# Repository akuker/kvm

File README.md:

# kvm
Keyboard Video Monitor switch for vintage computers

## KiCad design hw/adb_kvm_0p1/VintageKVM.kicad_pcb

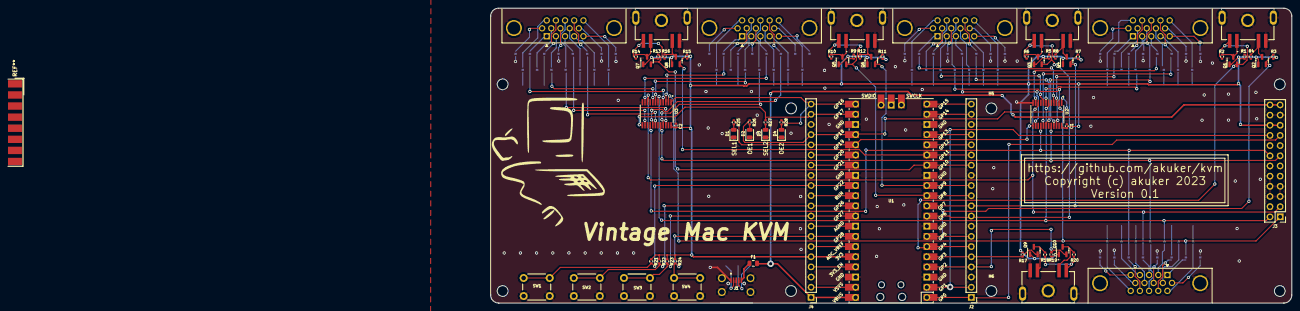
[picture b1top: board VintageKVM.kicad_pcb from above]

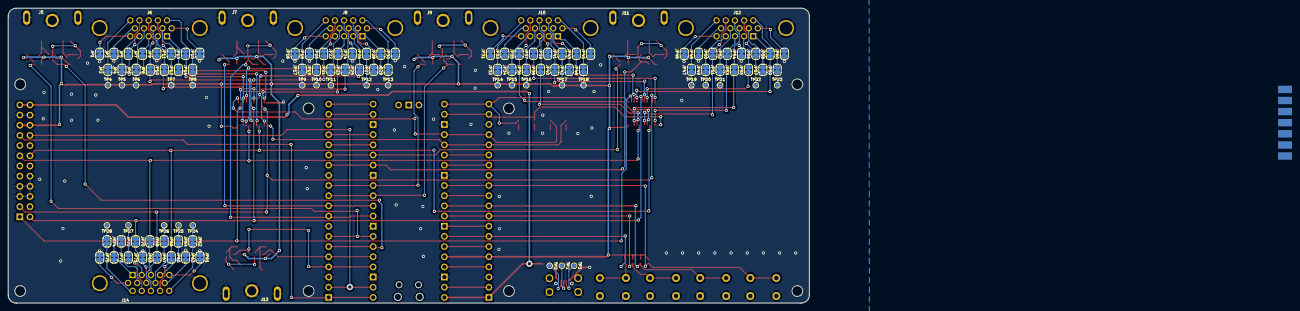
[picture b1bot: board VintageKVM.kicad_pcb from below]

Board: 2 copper layers, 200.0 x 73.6 mm, 177 parts (103 on the bottom side), 182 nets.

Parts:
C1, C2: 100nF; C_0402_1005Metric
D1, D2, D3, D4: LED_Small; LED_0805_2012Metric
F1: Polyfuse; Fuse_0805_2012Metric
H1, H2, H3, H4, H5, H6, H7, H8: MountingHole; MountingHole_2.7mm_M2.5
J1: Micro USB; U254051N4BH806
J2, J4: Conn_01x20_Pin; PinHeader_1x20_P2.54mm_Vertical
J3: Conn_02x10_Odd_Even; PinHeader_2x12_P2.54mm_Vertical
J5, J7, J9, J11, J13: CUI_MD2-40ST-SMT
J6, J8, J10, J12, J14: DE15_Receptacle_HighDensity_MountingHoles; DSUB-15-HD_Female_Horizontal_P2.29x1.98mm_EdgePinOffset3.03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
JP1, JP2, JP3, JP4, JP5, JP6, JP7, JP8, JP9, JP10, JP11, JP12, JP13, JP14, JP15, JP16, JP17, JP18, JP19, JP20, JP21, JP22, JP23, JP24, JP25, JP26, JP27, JP28, JP29, JP30, JP31, JP32, JP33, JP34, JP35, JP36, JP37, JP38, JP39, JP40, JP41, JP42, JP43, JP44, JP45, JP46, JP47, JP48, JP49, JP50, JP51, JP52, JP53, JP54, JP55, JP56, JP57, JP58, JP59, JP60, JP61, JP62, JP63, JP64, JP65, JP66, JP67, JP68, JP69, JP70, JP71, JP72, JP73, JP74, JP75: SolderJumper_2_Bridged; SolderJumper-2_P1.3mm_Bridged_RoundedPad1.0x1.5mm
Q1, Q2, Q3, Q4, Q5, Q6, Q7, Q8, Q9, Q10: BSS138; SOT-23
R1, R2, R3, R4, R5, R6, R7, R8, R9, R10, R11, R12, R13, R14, R15, R16, R17, R18, R19, R20, R21, R22, R23, R24, R25, R26, R27, R28: 10k; R_0402_1005Metric
SW1, SW2, SW3, SW4: SW_Push; SW_PUSH_6mm
TP1, TP2, TP3: TestPoint_Pad_D1.0mm
TP4, TP5, TP6, TP7, TP8, TP9, TP10, TP11, TP12, TP13, TP14, TP15, TP16, TP17, TP18, TP19, TP20, TP21, TP22, TP23, TP24, TP25, TP26, TP27, TP28: TestPoint_Small; TestPoint_Pad_D1.0mm
U1: Pico; RPi_Pico_SMD_TH
U2, U3: TS5V522CPWR; SOP65P640X120-24N

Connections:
3v3_EN: J4.4, U1.37 (3V3_EN)
+3V3: C1.1, C2.1, J3.19, J3.20, J4.5, Q1.1 (G), Q2.1 (G), Q3.1 (G), Q4.1 (G), Q5.1 (G), Q6.1 (G), Q7.1 (G), Q8.1 (G), Q9.1 (G), Q10.1 (G), R1.1, R3.1, R5.1, R7.1, R9.1, R11.1, R13.1, R15.1, R17.1, R19.1, R21.1, R22.1, R23.1, R24.1, U1.36 (3V3), U2.24 (VCC), U3.24 (VCC)
/Control Port/ADB_EXT_5v: J13.3, R18.1, R20.1
/Control Port/ADB_EXT_DATA: J13.1, Q10.3 (D), R20.2
/Control Port/ADB_EXT_PWR_ON: J13.2, Q9.3 (D), R18.2
/Input Port 1/ADB_EXT_5v: J5.3, R2.1, R4.1
/Input Port 1/ADB_EXT_DATA: J5.1, Q1.3 (D), R2.2
/Input Port 1/ADB_EXT_PWR_ON: J5.2, Q2.3 (D), R4.2
/Input Port 2/ADB_EXT_5v: J7.3, R6.1, R8.1
/Input Port 2/ADB_EXT_DATA: J7.1, Q3.3 (D), R6.2
/Input Port 2/ADB_EXT_PWR_ON: J7.2, Q4.3 (D), R8.2
/Input Port 3/ADB_EXT_5v: J9.3, R10.1, R12.1
/Input Port 3/ADB_EXT_DATA: J9.1, Q5.3 (D), R10.2
/Input Port 3/ADB_EXT_PWR_ON: J9.2, Q6.3 (D), R12.2
/Input Port 4/ADB_EXT_5v: J11.3, R14.1, R16.1
/Input Port 4/ADB_EXT_DATA: J11.1, Q7.3 (D), R14.2
/Input Port 4/ADB_EXT_PWR_ON: J11.2, Q8.3 (D), R16.2
ADC_VREF: J4.6, U1.35 (ADC_VREF)
AGND: J4.8, U1.33 (AGND)
CTRL_PORT_ADB_DATA: J2.5, Q9.2 (S), R17.2, U1.5 (GPIO3)
CTRL_PORT_ADB_PWR_ON: J2.4, Q10.2 (S), R19.2, U1.4 (GPIO2)
CTRL_PORT_BLUE: J3.3, JP67.1 (A), U2.10 (AB), U3.10 (AB)
CTRL_PORT_GREEN: J3.2, JP70.1 (A), U2.6 (AG), U3.6 (AG)
CTRL_PORT_HSYNC: J3.13, JP68.1 (A), U2.20 (ASCL), U3.20 (ASCL)
CTRL_PORT_RED: J3.1, JP73.1 (A), U2.2 (AR), U3.2 (AR)
CTRL_PORT_VSYNC: J3.14, JP65.1 (A), U2.16 (ASCA), U3.16 (ASCA)
GND: C1.2, C2.2, D1.1 (K), D2.1 (K), D3.1 (K), D4.1 (K), J1.1, J1.MH1, J1.MH2, J1.MH3, J1.MH4, J2.3, J2.8, J2.13, J2.18, J3.5, J3.6, J3.7, J3.8, J3.10, J3.21, J3.22, J4.3, J4.13, J4.18, J5.4, J5.S1 (SHIELD), J5.S2 (SHIELD), J5.S3 (SHIELD), J6.0, J7.4, J7.S1 (SHIELD), J7.S2 (SHIELD), J7.S3 (SHIELD), J8.0, J9.4, J9.S1 (SHIELD), J9.S2 (SHIELD), J9.S3 (SHIELD), J10.0, J11.4, J11.S1 (SHIELD), J11.S2 (SHIELD), J11.S3 (SHIELD), J12.0, J13.4, J13.S1 (SHIELD), J13.S2 (SHIELD), J13.S3 (SHIELD), J14.0, JP1.1 (A), JP3.1 (A), JP9.1 (A), JP12.1 (A), JP15.1 (A), JP16.1 (A), JP18.1 (A), JP24.1 (A), JP27.1 (A), JP30.1 (A), JP31.1 (A), JP33.1 (A), JP39.1 (A), JP42.1 (A), JP45.1 (A), JP46.1 (A), JP48.1 (A), JP54.1 (A), JP57.1 (A), JP60.1 (A), JP61.1 (A), JP63.1 (A), JP69.1 (A), JP72.1 (A), JP75.1 (A), SW1.1, SW2.1, SW3.1, SW4.1, U1.3 (GND), U1.8 (GND), U1.13 (GND), U1.18 (GND), U1.23 (GND), U1.28 (GND), U1.38 (GND), U2.12 (GND), U3.12 (GND)
GPIO14: J2.19, U1.19 (GPIO14)
GPIO15: J2.20, U1.20 (GPIO15)
GPIO20: J4.15, U1.26 (GPIO20)
GPIO21: J4.14, U1.27 (GPIO21)
GPIO22: J4.12, R21.2, SW1.2, U1.29 (GPIO22)
GPIO26: J4.10, R22.2, SW2.2, U1.31 (GPIO26_ADC0)
GPIO27: J4.9, R23.2, SW3.2, U1.32 (GPIO27_ADC1)
GPIO28: J4.7, R24.2, SW4.2, U1.34 (GPIO28_ADC2)
I2C0_SCL: J2.2, J3.18, U1.2 (GPIO1)
I2C0_SDA: J2.1, J3.17, U1.1 (GPIO0)
unnamed: D1.2 (A), R25.2
unnamed: D2.2 (A), R26.2
unnamed: D3.2 (A), R27.2
unnamed: D4.2 (A), R28.2
unnamed: F1.1, J1.5
unnamed: J1.2, TP1.1
unnamed: J1.3, TP2.1
unnamed: J1.4, TP3.1
unnamed: J6.5, JP1.2 (B)
unnamed: JP2.1 (A), TP4.1
unnamed: J6.15, JP2.2 (B)
unnamed: J6.10, JP3.2 (B)
unnamed: JP4.1 (A), TP5.1
unnamed: J6.4, JP4.2 (B)
unnamed: J6.14, JP5.2 (B)
unnamed: JP6.1 (A), TP6.1
unnamed: J6.9, JP6.2 (B)
unnamed: J6.3, JP7.2 (B)
unnamed: J6.13, JP8.2 (B)
unnamed: J6.8, JP9.2 (B)
unnamed: J6.2, JP10.2 (B)
unnamed: JP11.1 (A), TP7.1
unnamed: J6.12, JP11.2 (B)
unnamed: J6.7, JP12.2 (B)
unnamed: J6.1, JP13.2 (B)
unnamed: JP14.1 (A), TP8.1
unnamed: J6.11, JP14.2 (B)
unnamed: J6.6, JP15.2 (B)
unnamed: J8.5, JP16.2 (B)
unnamed: JP17.1 (A), TP9.1
unnamed: J8.15, JP17.2 (B)
unnamed: J8.10, JP18.2 (B)
unnamed: JP19.1 (A), TP10.1
unnamed: J8.4, JP19.2 (B)
unnamed: J8.14, JP20.2 (B)
unnamed: JP21.1 (A), TP11.1
unnamed: J8.9, JP21.2 (B)
unnamed: J8.3, JP22.2 (B)
unnamed: J8.13, JP23.2 (B)
unnamed: J8.8, JP24.2 (B)
unnamed: J8.2, JP25.2 (B)
unnamed: JP26.1 (A), TP12.1
unnamed: J8.12, JP26.2 (B)
unnamed: J8.7, JP27.2 (B)
unnamed: J8.1, JP28.2 (B)
unnamed: JP29.1 (A), TP13.1
unnamed: J8.11, JP29.2 (B)
unnamed: J8.6, JP30.2 (B)
unnamed: J10.5, JP31.2 (B)
unnamed: JP32.1 (A), TP14.1
unnamed: J10.15, JP32.2 (B)
unnamed: J10.10, JP33.2 (B)
unnamed: JP34.1 (A), TP15.1
unnamed: J10.4, JP34.2 (B)
unnamed: J10.14, JP35.2 (B)
unnamed: JP36.1 (A), TP16.1
unnamed: J10.9, JP36.2 (B)
unnamed: J10.3, JP37.2 (B)
unnamed: J10.13, JP38.2 (B)
unnamed: J10.8, JP39.2 (B)
unnamed: J10.2, JP40.2 (B)
unnamed: JP41.1 (A), TP17.1
unnamed: J10.12, JP41.2 (B)
unnamed: J10.7, JP42.2 (B)
unnamed: J10.1, JP43.2 (B)
unnamed: JP44.1 (A), TP18.1
unnamed: J10.11, JP44.2 (B)
unnamed: J10.6, JP45.2 (B)
unnamed: J12.5, JP46.2 (B)
unnamed: JP47.1 (A), TP19.1
unnamed: J12.15, JP47.2 (B)
unnamed: J12.10, JP48.2 (B)
unnamed: JP49.1 (A), TP20.1
unnamed: J12.4, JP49.2 (B)
unnamed: J12.14, JP50.2 (B)
unnamed: JP51.1 (A), TP21.1
unnamed: J12.9, JP51.2 (B)
unnamed: J12.3, JP52.2 (B)
unnamed: J12.13, JP53.2 (B)
unnamed: J12.8, JP54.2 (B)
unnamed: J12.2, JP55.2 (B)
unnamed: JP56.1 (A), TP22.1
unnamed: J12.12, JP56.2 (B)
unnamed: J12.7, JP57.2 (B)
unnamed: J12.1, JP58.2 (B)
unnamed: JP59.1 (A), TP23.1
unnamed: J12.11, JP59.2 (B)
unnamed: J12.6, JP60.2 (B)
unnamed: J14.5, JP61.2 (B)
unnamed: JP62.1 (A), TP24.1
unnamed: J14.15, JP62.2 (B)
unnamed: J14.10, JP63.2 (B)
unnamed: JP64.1 (A), TP25.1
unnamed: J14.4, JP64.2 (B)
unnamed: J14.14, JP65.2 (B)
unnamed: JP66.1 (A), TP26.1
unnamed: J14.9, JP66.2 (B)
unnamed: J14.3, JP67.2 (B)
unnamed: J14.13, JP68.2 (B)
unnamed: J14.8, JP69.2 (B)
unnamed: J14.2, JP70.2 (B)
unnamed: JP71.1 (A), TP27.1
unnamed: J14.12, JP71.2 (B)
unnamed: J14.7, JP72.2 (B)
unnamed: J14.1, JP73.2 (B)
unnamed: JP74.1 (A), TP28.1
unnamed: J14.11, JP74.2 (B)
unnamed: J14.6, JP75.2 (B)
OE_U1: J4.17, R26.1, U1.24 (GPIO18), U2.1 (OE)
OE_U2: J4.20, R28.1, U1.21 (GPIO16), U3.1 (OE)
PORT_1_ADB_DATA: J2.7, Q2.2 (S), R3.2, U1.7 (GPIO5)
PORT_1_ADB_PWR_ON: J2.6, Q1.2 (S), R1.2, U1.6 (GPIO4)
PORT_1_BLUE: JP7.1 (A), U2.11 (1B)
PORT_1_GREEN: JP10.1 (A), U2.7 (1G)
PORT_1_HSYNC: JP8.1 (A), U2.21 (1SCL)
PORT_1_RED: JP13.1 (A), U2.3 (1R)
PORT_1_VSYNC: JP5.1 (A), U2.17 (1SCA)
PORT_2_ADB_DATA: J2.10, Q4.2 (S), R7.2, U1.10 (GPIO7)
PORT_2_ADB_PWR_ON: J2.9, Q3.2 (S), R5.2, U1.9 (GPIO6)
PORT_2_BLUE: JP22.1 (A), U2.14 (2B)
PORT_2_GREEN: JP25.1 (A), U2.8 (2G)
PORT_2_HSYNC: JP23.1 (A), U2.22 (2SCL)
PORT_2_RED: JP28.1 (A), U2.4 (2R)
PORT_2_VSYNC: JP20.1 (A), U2.18 (2SCA)
PORT_3_ADB_DATA: J2.12, Q6.2 (S), R11.2, U1.12 (GPIO9)
PORT_3_ADB_PWR_ON: J2.11, Q5.2 (S), R9.2, U1.11 (GPIO8)
PORT_3_BLUE: JP37.1 (A), U3.11 (1B)
PORT_3_GREEN: JP40.1 (A), U3.7 (1G)
PORT_3_HSYNC: JP38.1 (A), U3.21 (1SCL)
PORT_3_RED: JP43.1 (A), U3.3 (1R)
PORT_3_VSYNC: JP35.1 (A), U3.17 (1SCA)
PORT_4_ADB_DATA: J2.15, Q8.2 (S), R15.2, U1.15 (GPIO11)
PORT_4_ADB_PWR_ON: J2.14, Q7.2 (S), R13.2, U1.14 (GPIO10)
PORT_4_BLUE: JP52.1 (A), U3.14 (2B)
PORT_4_GREEN: JP55.1 (A), U3.8 (2G)
PORT_4_HSYNC: JP53.1 (A), U3.22 (2SCL)
PORT_4_RED: JP58.1 (A), U3.4 (2R)
PORT_4_VSYNC: JP50.1 (A), U3.18 (2SCA)
RUN: J4.11, U1.30 (RUN)
SEL_U1: J4.16, R25.1, U1.25 (GPIO19), U2.13 (SEL)
SEL_U2: J4.19, R27.1, U1.22 (GPIO17), U3.13 (SEL)
UART0_RX: J2.17, U1.17 (GPIO13)
UART0_TX: J2.16, U1.16 (GPIO12)
VBUS: F1.2, J3.23, J3.24, J4.1, U1.40 (VBUS)
VSYS: J4.2, U1.39 (VSYS)

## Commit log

2023-03-17 v0.1 adb kvm
2023-03-29 baseline pio config
2023-03-29 basic selection logic
2023-03-29 revert file
2023-04-04 fixed selection logic

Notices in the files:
hw/adb_kvm_0p1/VintageKVM.kicad_pcb:
Copyright (c) akuker 2023
